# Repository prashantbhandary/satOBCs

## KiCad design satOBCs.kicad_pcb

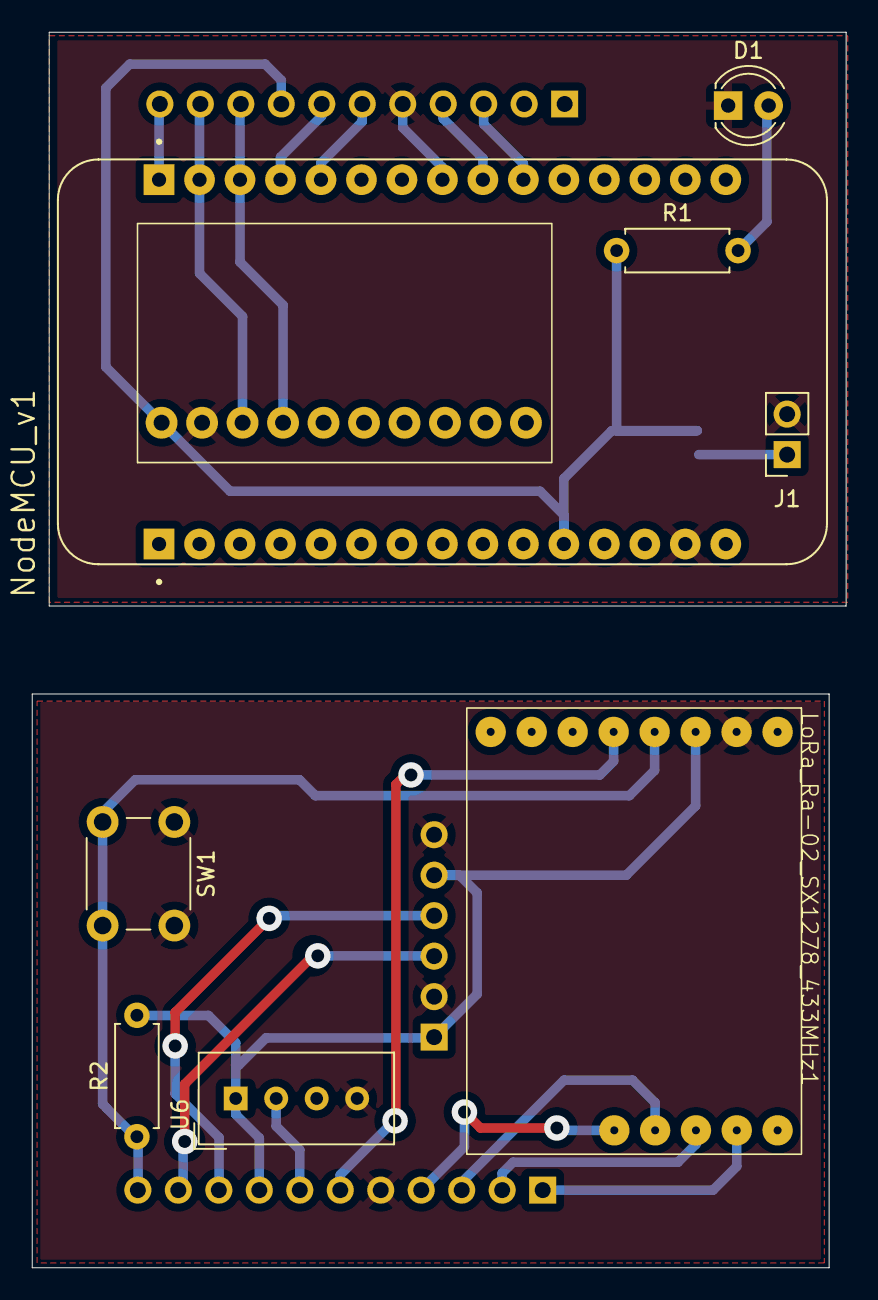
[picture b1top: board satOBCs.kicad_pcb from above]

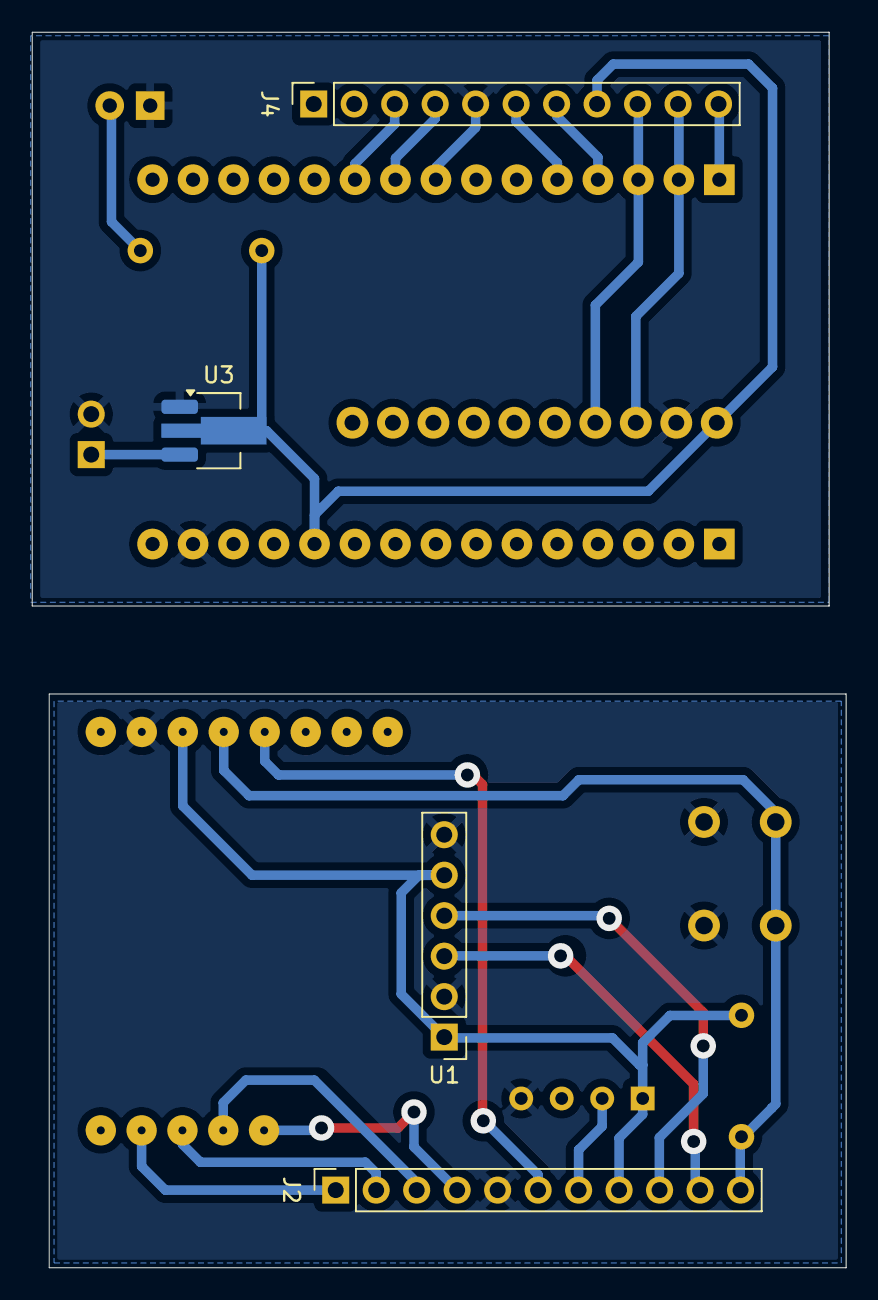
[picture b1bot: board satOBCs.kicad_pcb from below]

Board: 2 copper layers, 51.1 x 77.5 mm, 13 parts (4 on the bottom side), 13 nets.

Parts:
D1: LED; LED_D4.0mm
J1: Battery power; PinSocket_1x02_P2.54mm_Vertical
J2, J4: Conn_01x11_Pin; PinSocket_1x11_P2.54mm_Vertical
LoRa_Ra-02_SX1278_433MHz1: LORA-02
NodeMCU_v1: nodemcu
R1, R2: R; R_Axial_DIN0207_L6.3mm_D2.5mm_P7.62mm_Horizontal
SW1: SW_Push; SW_PUSH_6mm
U1: BMP280; PinHeader_1x06_P2.54mm_Vertical
U2: mpu-9250; mpu9250
U3: AZ1117-3.3; SOT-89-3_Handsoldering
U6: DHT11; Aosong_DHT11_5.5x12.0_P2.54mm

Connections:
+3V3: J2.8, J4.8, LoRa_Ra-02_SX1278_433MHz1.5 (3.3V), NodeMCU_v1.11 (3V), R1.1, R2.2, U1.1 (VCC), U1.5 (CSB), U2.1 (VCC), U3.2 (VO), U6.1 (VDD)
/CS: J2.1, J4.1, LoRa_Ra-02_SX1278_433MHz1.4 (NSS), NodeMCU_v1.20 (D8)
/D3: J2.6, J4.6, LoRa_Ra-02_SX1278_433MHz1.9 (DIO0), NodeMCU_v1.26 (D4)
/DHT_data: J2.7, J4.7, NodeMCU_v1.27 (D3), U6.2 (DATA)
/MISO: J2.3, J4.3, LoRa_Ra-02_SX1278_433MHz1.8 (MISO), NodeMCU_v1.22 (D6)
/MOSI: J2.2, J4.2, LoRa_Ra-02_SX1278_433MHz1.6 (MOSI), NodeMCU_v1.21 (D7)
/RST: J2.11, J4.11, LoRa_Ra-02_SX1278_433MHz1.7 (RST), NodeMCU_v1.30 (D0), R2.1, SW1.2
/SCL: J2.10, J4.10, NodeMCU_v1.29 (D1), U1.3 (SCL), U2.3 (SCL)
/SCLK: J2.4, J4.4, LoRa_Ra-02_SX1278_433MHz1.10 (SCK), NodeMCU_v1.23 (D5)
/SDA: J2.9, J4.9, NodeMCU_v1.28 (D2), U1.4 (SDA), U2.4 (SDA)
/VIN: J1.1, U3.3 (VI)
GND: D1.1 (K), J1.2, J2.5, J4.5, LoRa_Ra-02_SX1278_433MHz1.3 (GND), NodeMCU_v1.14 (G), SW1.1, U1.2 (GND), U1.6 (SDO), U2.2 (GND), U3.1 (GND), U6.4 (GND)
unnamed: D1.2 (A), R1.2

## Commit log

2026-01-03 added files
2026-01-03 added 2
2026-01-03 3rd time commit
2026-01-03 4th edited
2026-01-10 added last
